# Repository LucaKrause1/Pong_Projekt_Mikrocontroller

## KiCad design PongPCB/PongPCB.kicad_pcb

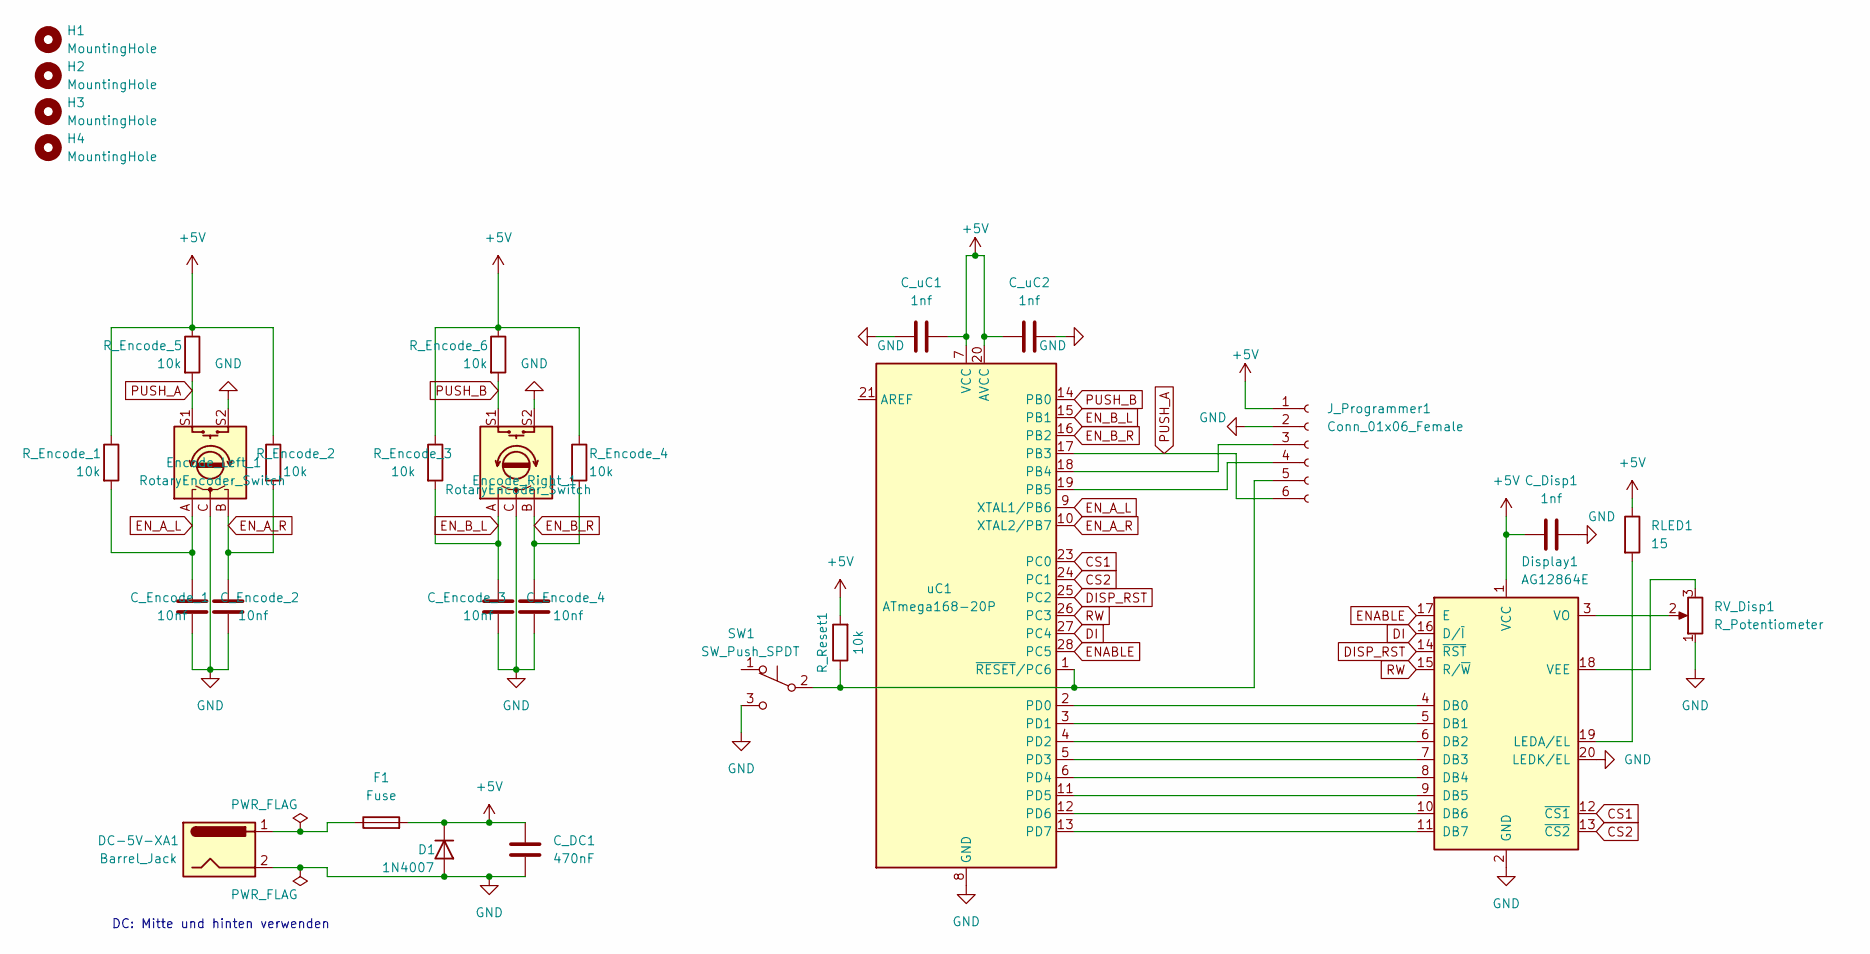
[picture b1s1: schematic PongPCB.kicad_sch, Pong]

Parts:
C_DC1: 470nF; C_Disc_D7.5mm_W2.5mm_P5.00mm
C_Disp1: 1nf; C_Disc_D5.0mm_W2.5mm_P2.50mm
C_Encode_1, C_Encode_2, C_Encode_3, C_Encode_4: 10nf; C_Disc_D5.0mm_W2.5mm_P2.50mm
C_uC1, C_uC2: 1nf; C_Disc_D5.0mm_W2.5mm_P2.50mm
D1: 1N4007; D_DO-41_SOD81_P10.16mm_Horizontal
DC-5V-XA1: Barrel_Jack; BarrelJack_GCT_DCJ200-10-A_Horizontal
Display1: AG12864E
Encode_Left_1: RotaryEncoder_Switch; RotaryEncoder_Alps_EC11E-Switch_Vertical_H20mm
Encode_Right_1: RotaryEncoder_Switch; RotaryEncoder_Alps_EC11E-Switch_Vertical_H20mm
F1: Fuse; Sicherung
H1, H2, H3, H4: MountingHole; MountingHole_3.2mm_M3
J_Programmer1: Conn_01x06_Female; PinHeader_1x06_P2.54mm_Horizontal
RLED1: 15; R_Axial_DIN0309_L9.0mm_D3.2mm_P15.24mm_Horizontal
RV_Disp1: R_Potentiometer; Potentiometer_Piher_PT-10-V10_Vertical_Hole
R_Encode_1, R_Encode_2, R_Encode_3, R_Encode_4, R_Encode_5, R_Encode_6: 10k; R_Axial_DIN0309_L9.0mm_D3.2mm_P15.24mm_Horizontal
R_Reset1: 10k; R_Axial_DIN0309_L9.0mm_D3.2mm_P15.24mm_Horizontal
SW1: SW_Push_SPDT; Eingabetaste
uC1: ATmega168-20P; DIP-28_W7.62mm

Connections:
+5V: C_DC1.1, C_Disp1.1, C_uC1.1, C_uC2.2, D1.1 (K), Display1.1 (VCC), F1.2, J_Programmer1.1, RLED1.1, R_Encode_1.1, R_Encode_2.1, R_Encode_3.1, R_Encode_4.1, R_Encode_5.1, R_Encode_6.1, R_Reset1.2, uC1.7 (VCC), uC1.20 (AVCC)
CS1: Display1.12 (~CS1), uC1.23 (PC0)
CS2: Display1.13 (~CS2), uC1.24 (PC1)
DI: Display1.16 (D/~I), uC1.27 (PC4)
DISP_RST: Display1.14 (~RST), uC1.25 (PC2)
ENABLE: Display1.17 (E), uC1.28 (PC5)
EN_A_L: C_Encode_1.1, Encode_Left_1.A, R_Encode_1.2, uC1.9 (XTAL1/PB6)
EN_A_R: C_Encode_2.1, Encode_Left_1.B, R_Encode_2.2, uC1.10 (XTAL2/PB7)
EN_B_L: C_Encode_3.1, Encode_Right_1.A, R_Encode_3.2, uC1.15 (PB1)
EN_B_R: C_Encode_4.1, Encode_Right_1.B, R_Encode_4.2, uC1.16 (PB2)
GND: C_DC1.2, C_Disp1.2, C_Encode_1.2, C_Encode_2.2, C_Encode_3.2, C_Encode_4.2, C_uC1.2, C_uC2.1, D1.2 (A), DC-5V-XA1.2, Display1.2 (GND), Display1.20 (LEDK/EL), Encode_Left_1.C, Encode_Left_1.S2, Encode_Right_1.C, Encode_Right_1.S2, J_Programmer1.2, RV_Disp1.1, SW1.3 (C), uC1.8 (GND), uC1.22 (GND)
unnamed: DC-5V-XA1.1, F1.1
unnamed: Display1.3 (VO), RV_Disp1.2
unnamed: Display1.4 (DB0), uC1.2 (PD0)
unnamed: Display1.5 (DB1), uC1.3 (PD1)
unnamed: Display1.6 (DB2), uC1.4 (PD2)
unnamed: Display1.7 (DB3), uC1.5 (PD3)
unnamed: Display1.8 (DB4), uC1.6 (PD4)
unnamed: Display1.9 (DB5), uC1.11 (PD5)
unnamed: Display1.10 (DB6), uC1.12 (PD6)
unnamed: Display1.11 (DB7), uC1.13 (PD7)
unnamed: Display1.18 (VEE), RV_Disp1.3
unnamed: Display1.19 (LEDA/EL), RLED1.2
unnamed: J_Programmer1.3, uC1.18 (PB4)
unnamed: J_Programmer1.4, uC1.19 (PB5)
unnamed: J_Programmer1.5, R_Reset1.1, SW1.2 (B), uC1.1 (~RESET/PC6)
PUSH_A: Encode_Left_1.S1, J_Programmer1.6, R_Encode_5.2, uC1.17 (PB3)
PUSH_B: Encode_Right_1.S1, R_Encode_6.2, uC1.14 (PB0)
RW: Display1.15 (R/~W), uC1.26 (PC3)

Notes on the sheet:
DC: Mitte und hinten verwenden

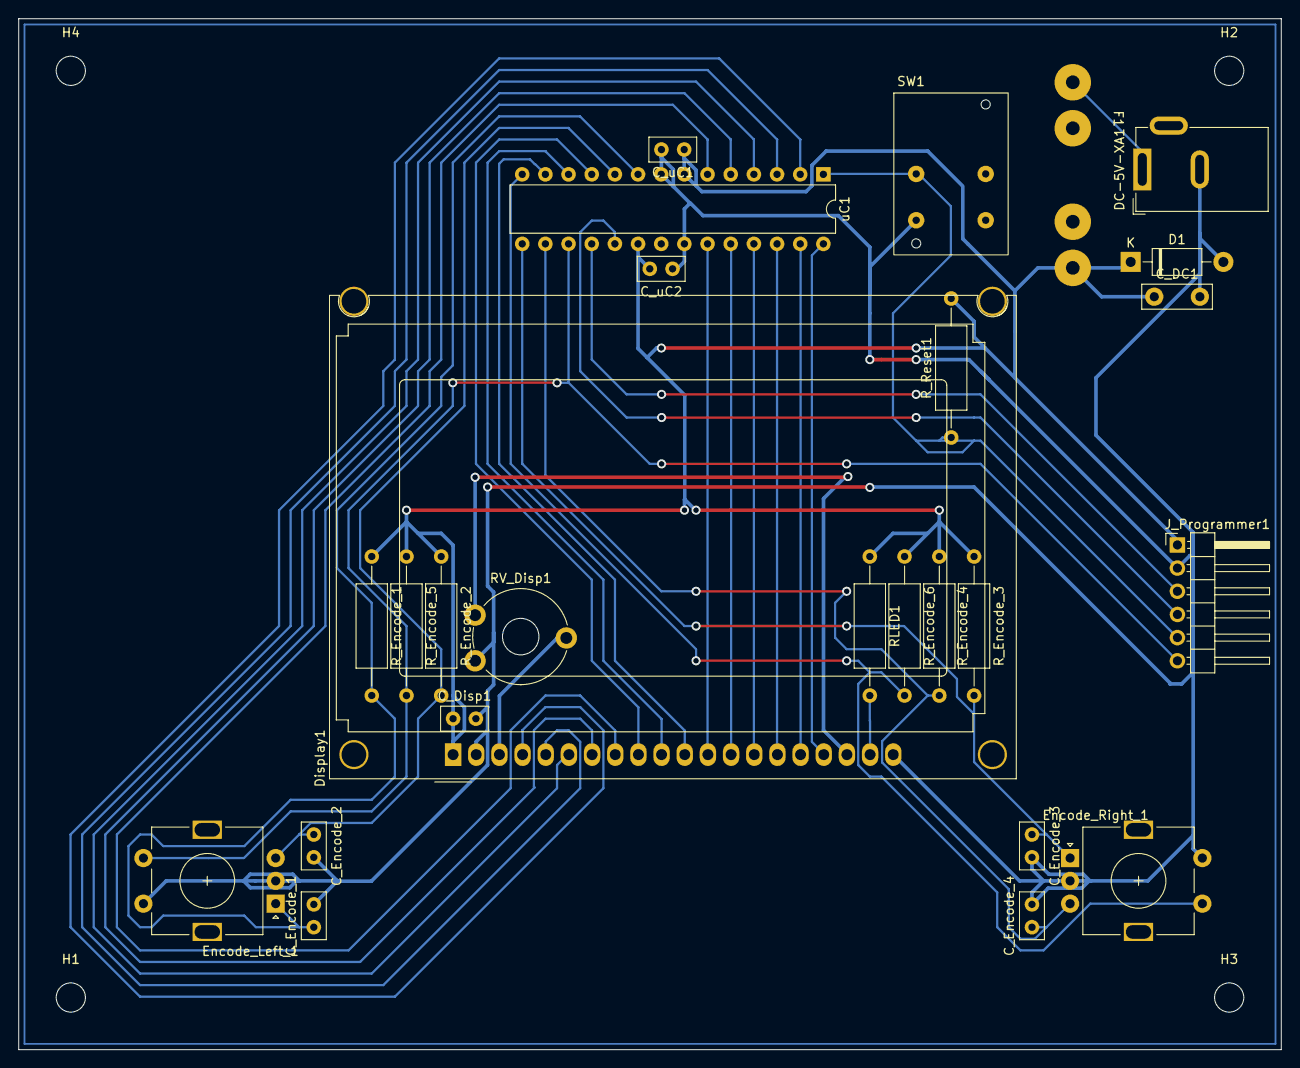
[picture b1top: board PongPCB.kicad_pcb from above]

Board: 2 copper layers, 138.4 x 113.0 mm, 30 parts (0 on the bottom side), 29 nets.

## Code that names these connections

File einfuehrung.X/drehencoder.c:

/* 
 * File:   drehencoder.c
 * Author: Luca Krause
 *
 * Created on 21. April 2022, 14:52
 */

#include "drehencoder.h"
#include "debug.h"
#include <avr/interrupt.h>

//noch zu handelnde Interrupts der Drehencoder
volatile signed int interruptCounterA = 0;
volatile signed int interruptCounterB = 0;

//Gibt die Werte der Drehencoder + deren Schalter zurück
#define GET_ENCODER_A ((PINB & 0b00000110)>>PB1)
#define GET_ENCODER_B ((PINB & 0b11000000)>>PB6)
#define GET_PUSH_A ((PINB & 0b00000001)>>PB0)
#define GET_PUSH_B ((PINB & 0b00001000)>>PB3)

//alte Zustände der Drehencoder + deren Schalter
static volatile char oldEncoderA = 0;
static volatile char oldEncoderB = 0;
static volatile unsigned char oldPushA = 0;
static volatile unsigned char oldPushB = 0;

//Zähler, wie lange ein Schläger schon/nicht mehr invertiert ist
static volatile char counterA = 0;
static volatile char counterB = 0;

//darf ein Schläger gerade umgedreht werden? 1 = true, 0 = false
static volatile char invertAChange = 1;
static volatile char invertBChange = 1;


//LUT der Drehencoder (alter und neuer Zustand als Eingabe)
static const signed char grayDecode[16] = {0,-1,1,0,1,0,0,-1,-1,0,0,1,0,1,-1,0};

/**
 * Startet die Pin-Change-Interrupts an den benötigten Pins
 */
static void startInterrupts(void) {
	PCICR |= (1<<PCIE0);
	PCMSK0 |= (1<<PCINT0) | (1<<PCINT1) | (1<<PCINT2) | (1<<PCINT3) | (1<<PCINT6) | (1<<PCINT7);
	sei();
}

/**
 * Startet den Timer, um den Timer für die Schlägerinvertierung zu aktivieren
 */
void startTimerPush(void) {    
    TCCR0B |= 1<<WGM02;// Timer im CTC-Mode mit OCR0A als Top
    TCCR0B |= 0b101; //Systemtakt durch 1024
    TIMSK0 |= 1<<OCIE0A;
    OCR0A = 255;
}

void initRotary(void) {
	//Input Pins
    ClearBit(DDRB, PCINT0);
	ClearBit(DDRB, PCINT1);
	ClearBit(DDRB, PCINT2);
    ClearBit(DDRB, PCINT3);
	//ClearMask(DDRB, PCINT4);
	ClearBit(DDRB, PCINT6);
	ClearBit(DDRB, PCINT7);
    oldEncoderA = GET_ENCODER_A;
    oldEncoderB = GET_ENCODER_B;
    oldPushA = GET_PUSH_A;
    oldPushB = GET_PUSH_B;
    startTimerPush();
	startInterrupts();
}

ISR(PCINT0_vect) {
    char encoderA = GET_ENCODER_A;
    char encoderB = GET_ENCODER_B;
    unsigned char indexA = (encoderA<<2)|(oldEncoderA);
    unsigned char indexB = (encoderB<<2)|(oldEncoderB);
    signed char resA = grayDecode[indexA];
    signed char resB = grayDecode[indexB];
    
    char pushA = GET_PUSH_A;
    char pushB = GET_PUSH_B;
    
    char A = pushA ^ oldPushA;
    char B = pushB ^ oldPushB;
    
    oldPushA = pushA;
    oldPushB = pushB;

    //darf der Schläger invertiert werden?
    if (A && invertAChange) {
        invertA = -1;
        invertAChange = 0;
    }
    if (B && invertBChange) {
        invertB = -1;
        invertBChange = 0;
    }
    
    interruptCounterB += resA;
    oldEncoderA = encoderA;
    interruptCounterA += resB;
    oldEncoderB = encoderB;
}

ISR(TIMER0_COMPA_vect) {
    //Zähler hochzählen wenn invertiert 
    //oder wenn gerade erst wieder in die richtige Richtung
    if (invertA == -1 || (!invertAChange && invertA == 1)) {
        counterA++;
    }
    if (invertB == -1 || (!invertBChange && invertB == 1)) {
        counterB++;
    }
    static const char max = 20;
    //zurückdrehen, aber weitere Drehung erstmal nicht erlauben
    if (!invertAChange && counterA == max) {
        if (invertA == 1) {
            invertAChange = 1;
        }
        invertA = 1;
        counterA = 0;
    }
    if (!invertBChange && counterB == max) {
        if (invertB == 1) {
            invertBChange = 1;
        }
        invertB = 1;
        counterB = 0;
    }
}

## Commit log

2022-08-01 initial commit. Dokumentation fast fertig. Code muss noch leicht überarbeitet werden.
